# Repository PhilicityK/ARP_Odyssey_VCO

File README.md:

ARP_Odyssey_VCO

Modular Version of the ARP ODYSSEY MKII/III VCO

ABOUT THIS PROJECT

Dreaming of my own modular synthesizer for many years, I've decided to finally start a DIY project. First of all I wanted to build a module which allows me to create sounds. I mean what’s the most exited thing about synthesizers? Right! Turning knobs, altering sounds and waveforms! ;) Therefore I have chosen to build the VCO from an ARP ODYSSEY MKII. If you are not familiar with the ODYSSEY just head over to Youtube and have a quick listen to it. It sounds awesome! :)

ABOUT THE CIRCUIT

The great thing about vintage electronics is the availability of official service and repair manuals. I’ve found one for the ARP ODYSSEY online:
http://www.arpodyssey.com/manuals/Arp%20Odyssey%20Service%20Manual.pdf

With the original schematics at my fingertips it was fairly easy to find the VCO section. I’ve used the latest version of EAGLE (7.7.0) to rebuild the circuit. My goal was to keep it simple by using parts which are still available and easily obtainable. I was able to get everything at my distributor of choice (www.reichelt.de). The VCO operates at +/-15V. It might be possible to use it with +/-12V to create sounds, but at lower voltages the CV-tracking will be most likely inaccurate.
This thread over at electro-music gave me a few ideas on how to design my front panel: 
http://files.electro-music.com/forum/topic-54502.html

BUILDING PROCESS

The PCB is home etched and drilled on my DIY CNC machine. 
Soldering is done with an ERSA soldering iron.
The front panel is created from black acrylic which is CNC machined as well.
I’ve used a white pen with a fine tip to fill in the engraved font.

Have a look at the wiki for further informations on building this module.

IMPORTANT

I have not created the schematics for the ARP Odyssey MKII/III VCO. I have just reworked the layout for all the DIY synth builders out there.

Copyright exists (Rhodes/CBS/ARP). No infringement is intended. The files are for experimental and educational purposes only. All the credits for the schematics go to the copyright holder.

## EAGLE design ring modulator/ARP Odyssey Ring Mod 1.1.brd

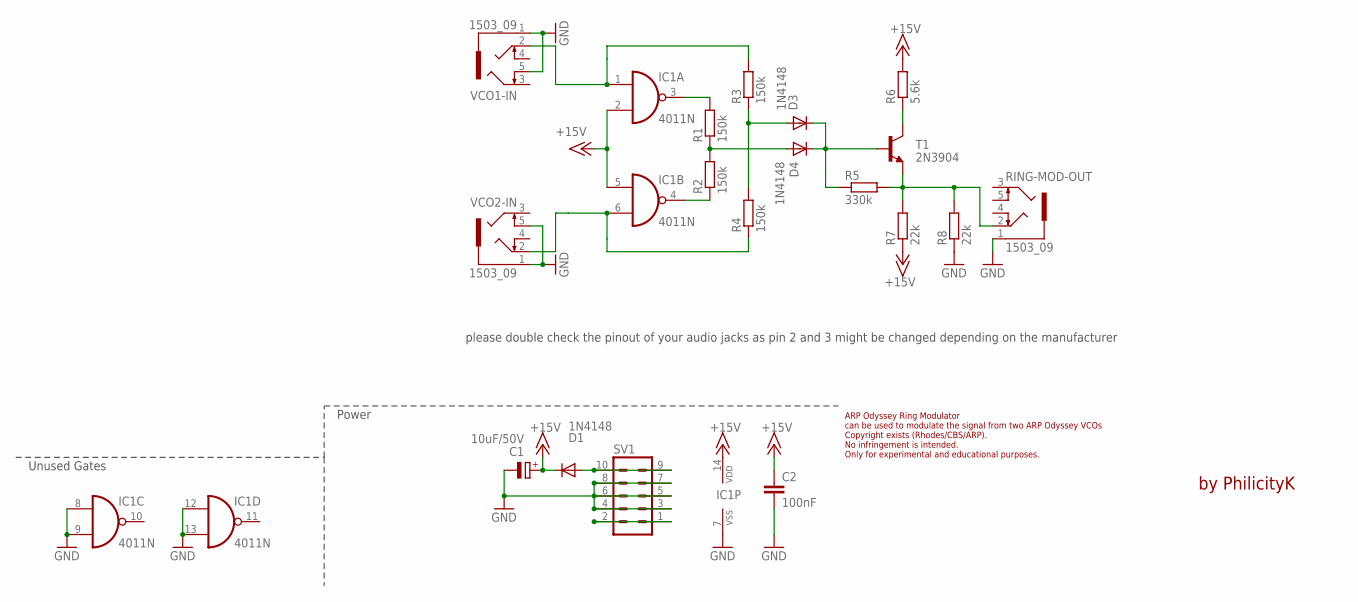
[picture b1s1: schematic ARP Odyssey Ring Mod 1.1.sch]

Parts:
C1: 10uF/50V; E3,5-8
C2: 100nF; C050-024X044
D1, D3, D4: 1N4148; DO35-7
IC1: 4011N; DIL14
R1, R2, R3, R4: 150k; 0207/7
R5: 330k; 0207/7
R6: 5.6k; 0207/7
R7, R8: 22k; 0207/7
RING-MOD-OUT: 1503_09
SV1: ML10
T1: 2N3904; TO92-EBC
VCO1-IN, VCO2-IN: 1503_09

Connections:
+15V: C1.+, C2.1, D1.C, IC1.2 (I1), IC1.5 (I0), IC1.14 (VDD), R6.2, R7.1
GND: C1.-, C2.2, IC1.7 (VSS), IC1.8 (I0), IC1.9 (I1), IC1.12 (I0), IC1.13 (I1), R8.1, RING-MOD-OUT.1, SV1.3, SV1.4, SV1.5, SV1.6, SV1.7, SV1.8, VCO1-IN.1, VCO1-IN.5, VCO2-IN.1, VCO2-IN.5
unnamed: D1.A, SV1.9, SV1.10
unnamed: IC1.3 (O), R1.2
unnamed: IC1.4 (O), R2.1
unnamed: D4.A, R1.1, R2.2
unnamed: SV1.1, SV1.2
unnamed: R5.2, R7.2, R8.2, RING-MOD-OUT.2, T1.E
unnamed: IC1.6 (I1), R4.1, VCO2-IN.2
unnamed: IC1.1 (I0), R3.2, VCO1-IN.2
unnamed: D3.A, R3.1, R4.2
unnamed: D3.C, D4.C, R5.1, T1.B
unnamed: R6.1, T1.C

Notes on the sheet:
ARP Odyssey Ring Modulator can be used to modulate the signal from two ARP Odyssey VCOs Copyright exists (Rhodes/CBS/ARP). No infringement is intended. Only for experimental and educational purposes.
Unused Gates
Power
by PhilicityK
please double check the pinout of your audio jacks as pin 2 and 3 might be changed depending on the manufacturer

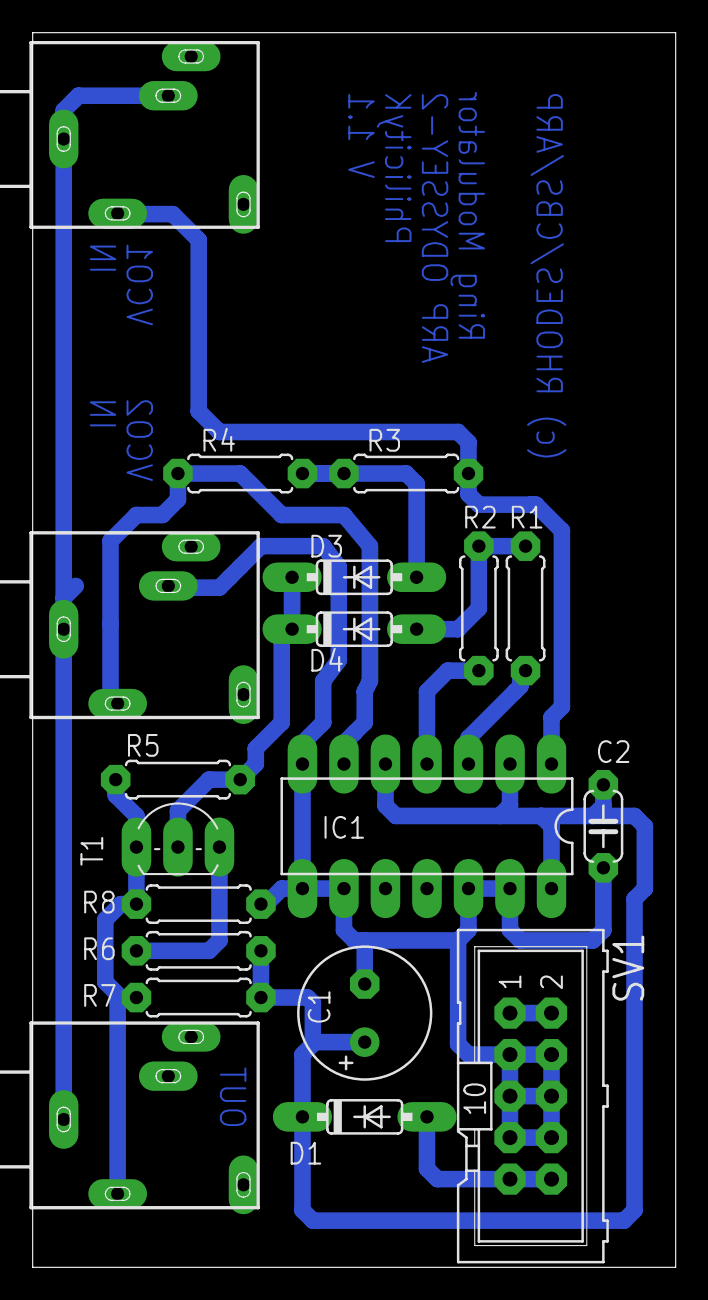
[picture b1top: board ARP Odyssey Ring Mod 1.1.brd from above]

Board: 2 copper layers, 39.4 x 75.6 mm, 19 parts (0 on the bottom side), 13 nets.

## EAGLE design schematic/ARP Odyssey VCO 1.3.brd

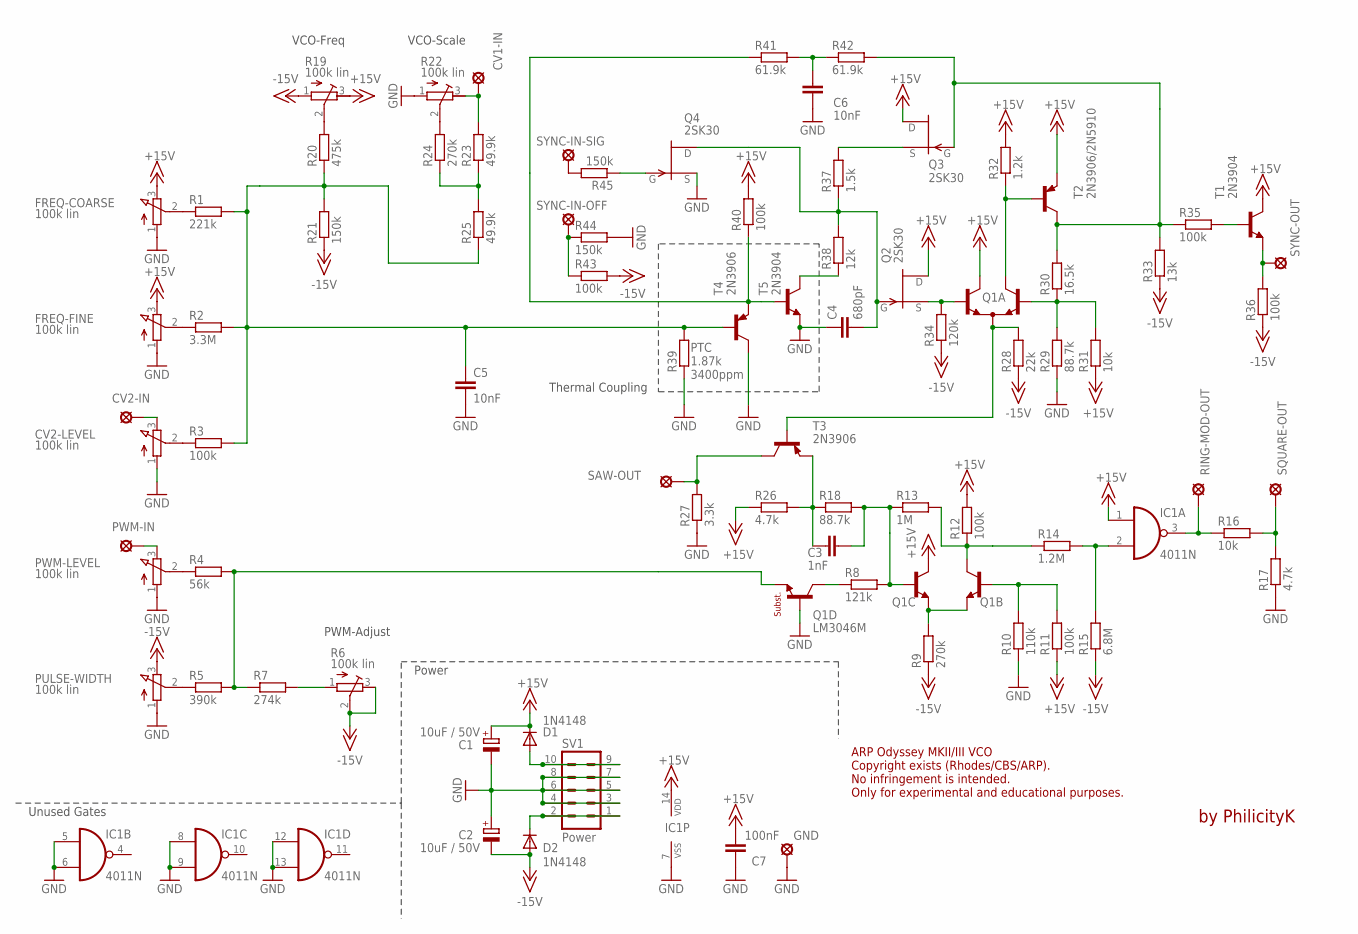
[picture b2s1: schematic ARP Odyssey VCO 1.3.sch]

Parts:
C1, C2: 10uF / 50V; E2,5-6E
C3: 1nF; C050-045X075
C4: 680pF; C050-045X075
C5, C6: 10nF; C050-045X075
C7: 100nF; C050-045X075
CV1-IN, CV2-IN: SE11
CV2-LEVEL: 100k lin; RK11K112
D1, D2: 1N4148; DO35-7
FREQ-COARSE: 100k lin; RK11K112
FREQ-FINE: 100k lin; RK11K112
GND: SE11
IC1: 4011N; DIL14
PULSE-WIDTH: 100k lin; RK11K112
PWM-IN: SE11
PWM-LEVEL: 100k lin; RK11K112
Q1: LM3046M; SO14
Q2, Q3, Q4: 2SK30; TO92
R1: 221k; 0207/7
R2: 3.3M; 0207/7
R3, R11, R12, R35, R36, R40, R43: 100k; 0207/7
R4: 56k; 0207/7
R5: 390k; 0207/7
R6, R19, R22: 100k lin; RTRIM64W
R7: 274k; 0207/7
R8: 121k; 0207/7
R9, R24: 270k; 0207/7
R10: 110k; 0207/7
R13: 1M; 0207/7
R14: 1.2M; 0207/7
R15: 6.8M; 0207/7
R16, R31: 10k; 0207/7
R17, R26: 4.7k; 0207/7
R18, R29: 88.7k; 0207/7
R20: 475k; 0207/7
R21, R44, R45: 150k; 0207/7
R23, R25: 49.9k; 0207/7
R27: 3.3k; 0207/7
R28: 22k; 0207/7
R30: 16.5k; 0207/7
R32: 1.2k; 0207/7
R33: 13k; 0207/7
R34: 120k; 0207/7
R37: 1.5k; 0207/7
R38: 12k; 0207/7
R39: PTC 1.87k; 0207/7
R41, R42: 61.9k; 0207/7
RING-MOD-OUT: SE11
SAW-OUT: SE11
SQUARE-OUT: SE11
SV1: Power; ML10
SYNC-IN-OFF: SE11
SYNC-IN-SIG: SE11
SYNC-OUT: SE11
T1, T5: 2N3904; TO92-EBC
T2: 2N3906/2N5910; TO92-EBC
T3, T4: 2N3906; TO92-EBC

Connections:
+15V: C1.+, C7.2, D1.C, FREQ-COARSE.3 (E), FREQ-FINE.3 (E), IC1.1 (I0), IC1.14 (VDD), Q1.5 (C2), Q1.11 (C), Q2.3 (D), Q3.3 (D), R11.2, R12.2, R19.3 (E), R26.1, R31.2, R32.2, R40.1, T1.C, T2.E
-15V: C2.-, D2.A, PULSE-WIDTH.3 (E), R6.2 (S), R6.3 (E), R9.1, R15.1, R19.1 (A), R21.2, R28.1, R33.1, R34.1, R36.2, R43.2
GND: C1.-, C2.+, C4.1, C5.2, C6.2, C7.1, CV2-LEVEL.1 (A), FREQ-COARSE.1 (A), FREQ-FINE.1 (A), GND.MP, IC1.5 (I0), IC1.6 (I1), IC1.7 (VSS), IC1.8 (I0), IC1.9 (I1), IC1.12 (I0), IC1.13 (I1), PULSE-WIDTH.1 (A), PWM-LEVEL.1 (A), Q1.12 (B), Q4.1 (S), R10.1, R17.1, R22.1 (A), R27.2, R29.1, R39.1, R44.2, SV1.3, SV1.4, SV1.5, SV1.6, SV1.7, SV1.8, T4.C, T5.E
unnamed: D2.C, SV1.1, SV1.2
unnamed: FREQ-COARSE.2 (S), R1.1
unnamed: FREQ-FINE.2 (S), R2.1
unnamed: C5.1, R1.2, R2.2, R3.2, R20.2, R21.1, R25.2, R39.2, T4.B
unnamed: D1.A, SV1.9, SV1.10
unnamed: CV2-LEVEL.2 (S), R3.1
unnamed: CV2-IN.MP, CV2-LEVEL.3 (E)
unnamed: PWM-IN.MP, PWM-LEVEL.3 (E)
unnamed: PWM-LEVEL.2 (S), R4.1
unnamed: PULSE-WIDTH.2 (S), R5.1
unnamed: Q1.13 (E), R4.2, R5.2, R7.1
unnamed: R6.1 (A), R7.2
unnamed: Q1.14 (C), R8.1
unnamed: C3.2, Q1.9 (B), R8.2, R13.1, R18.2
unnamed: Q1.7 (E), Q1.10 (E), R9.2
unnamed: Q1.6 (B), R10.2, R11.1
unnamed: Q1.8 (C), R12.1, R13.2, R14.1
unnamed: IC1.2 (I1), R14.2, R15.2
unnamed: IC1.3 (O), R16.1, RING-MOD-OUT.MP
unnamed: R16.2, R17.2, SQUARE-OUT.MP
unnamed: C3.1, R18.1, R26.2, T3.E
unnamed: R19.2 (S), R20.1
unnamed: R22.2 (S), R24.1
unnamed: R23.2, R24.2, R25.1
unnamed: CV1-IN.MP, R22.3 (E), R23.1
unnamed: Q1.3 (E), R28.2, T3.B
unnamed: R27.1, SAW-OUT.MP, T3.C
unnamed: Q1.2 (B1), R29.2, R30.1, R31.1
unnamed: Q3.2 (G), R30.2, R33.2, R35.2, R42.1, T2.C
unnamed: Q1.1 (C1), R32.1, T2.B
unnamed: Q1.4 (B2), Q2.1 (S), R34.2
unnamed: R36.1, SYNC-OUT.MP, T1.E
unnamed: R35.1, T1.B
unnamed: Q3.1 (S), R37.1
unnamed: C6.1, R41.1, R42.2
unnamed: R38.2, T5.C
unnamed: R40.2, R41.2, T4.E, T5.B
unnamed: R43.1, R44.1, SYNC-IN-OFF.MP
unnamed: Q4.2 (G), R45.1
unnamed: R45.2, SYNC-IN-SIG.MP
unnamed: C4.2, Q2.2 (G), Q4.3 (D), R37.2, R38.1

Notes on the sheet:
PWM-Adjust
VCO-Scale
VCO-Freq
Thermal Coupling
Unused Gates
Power
PTC 1.87k 3400ppm
ARP Odyssey MKII/III VCO Copyright exists (Rhodes/CBS/ARP). No infringement is intended. Only for experimental and educational purposes.
by PhilicityK

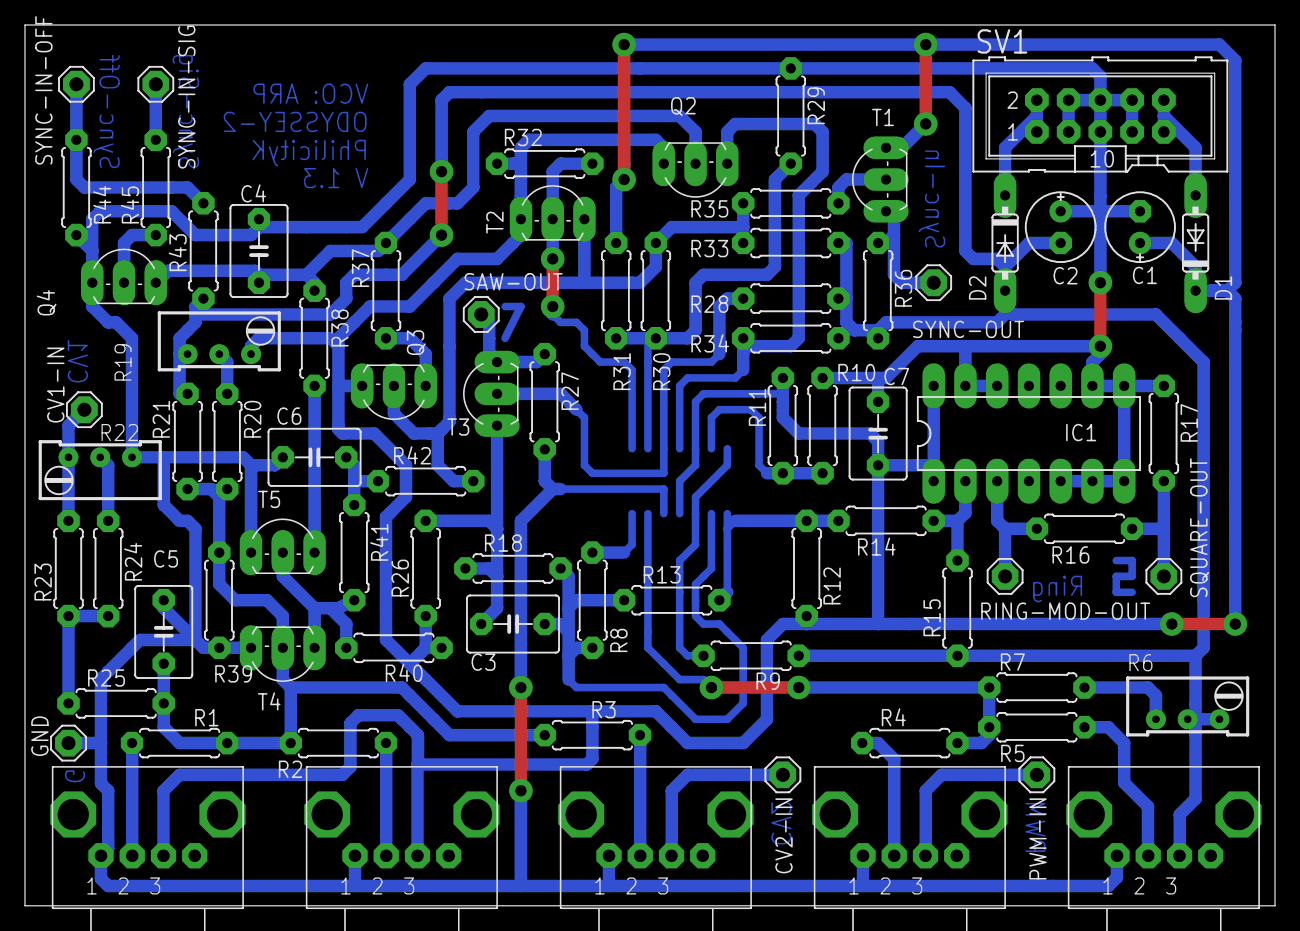
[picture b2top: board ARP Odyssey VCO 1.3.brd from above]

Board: 2 copper layers, 100.0 x 70.5 mm, 80 parts (1 on the bottom side), 44 nets.

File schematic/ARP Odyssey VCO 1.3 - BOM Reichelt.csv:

Qty;Value;Device;Package;Parts;Description;Reichelt; Total (Euro)
2;10uF / 50V;CPOL-EUE2,5-6E;E2,5-6E;C1, C2;POLARIZED CAPACITOR, European symbol;RAD FC 10/50;0,20
1;1nF;C-EU050-045X075;C050-045X075;C3;CAPACITOR, European symbol;FKP2-63 1,0N;0,13
1;680pF;C-EU050-045X075;C050-045X075;C4;CAPACITOR, European symbol;FKP2-100 680P;0,13
2;10nF;C-EU050-045X075;C050-045X075;C5, C6;CAPACITOR, European symbol;FKP2-63 10N;0,15
1;100nF;C-EU050-045X075;C050-045X075;C7;CAPACITOR, European symbol;MKS2-63 100N;0,13
5;100k lin;RK11K112;RK11K112;CV2-LEVEL, FREQ-COARSE, FREQ-FINE, PULSE-WIDTH, PWM-LEVEL;ALPS-Potentiometer;RK11K112-LIN100K;6,75
2;1N4148;1N4148DO35-7;DO35-7;D1, D2;DIODE;1N 4148;0,08
1;4011N;4011N;DIL14;IC1;Quad 2-input NAND;MOS 4011;0,24
1;LM3046M/NOPB;LM3046M/NOPB;SO14;Q1;Texas Instruments LM3046;LM 3046 M;0,80
3;2SK30;2SK30;TO92;Q2, Q3, Q4;Transistor N-FET;2SK 30;2,58
1;221k;R-EU_0207/7;0207/7;R1;RESISTOR, European symbol;METALL 221K;0,08
1;110k;R-EU_0207/7;0207/7;R10;RESISTOR, European symbol;METALL 110K;0,08
1;1M;R-EU_0207/7;0207/7;R13;RESISTOR, European symbol;METALL 1,00M;0,08
1;1.2M;R-EU_0207/7;0207/7;R14;RESISTOR, European symbol;METALL 1,20M;0,08
1;6.8M;R-EU_0207/7;0207/7;R15;RESISTOR, European symbol;METALL 6,80M;0,08
2;10k;R-EU_0207/7;0207/7;R16, R31;RESISTOR, European symbol;METALL 10,0K;0,16
2;4.7k;R-EU_0207/7;0207/7;R17, R26;RESISTOR, European symbol;METALL 4,70K;0,16
2;88.7k;R-EU_0207/7;0207/7;R18, R29;RESISTOR, European symbol;METALL 88,7K;0,16
1;3.3M;R-EU_0207/7;0207/7;R2;RESISTOR, European symbol;METALL 3,30M;0,08
1;475k;R-EU_0207/7;0207/7;R20;RESISTOR, European symbol;METALL 475K;0,08
3;150k;R-EU_0207/7;0207/7;R21, R44, R45;RESISTOR, European symbol;METALL 150K;0,25
2;49.9k;R-EU_0207/7;0207/7;R23, R25;RESISTOR, European symbol;METALL 49,9K;0,16
1;3.3k;R-EU_0207/7;0207/7;R27;RESISTOR, European symbol;METALL 3,30K;0,08
1;22k;R-EU_0207/7;0207/7;R28;RESISTOR, European symbol;METALL 22,0K;0,08
7 (10);100k;R-EU_0207/7;0207/7;R3, R11, R12, R35, R36, R40, R43;RESISTOR, European symbol (10pcs are cheaper than 7);METALL 100K;0,49
1;16.5k;R-EU_0207/7;0207/7;R30;RESISTOR, European symbol;METALL 16,5K;0,08
1;1.2k;R-EU_0207/7;0207/7;R32;RESISTOR, European symbol;METALL 1,20K;0,08
1;13k;R-EU_0207/7;0207/7;R33;RESISTOR, European symbol;METALL 13,0K;0,08
1;120k;R-EU_0207/7;0207/7;R34;RESISTOR, European symbol;METALL 120K;0,08
1;1.5k;R-EU_0207/7;0207/7;R37;RESISTOR, European symbol;METALL 1,50K;0,08
1;12k;R-EU_0207/7;0207/7;R38;RESISTOR, European symbol;METALL 12,0K;0,08
1;PTC 1.87k;R-EU_0207/7;0207/7;R39;PTC  (TEMPCO 1.87k 3400ppm would be better but isn't avaliable from Reichelt);KTY 81-210;0,63
1;56k;R-EU_0207/7;0207/7;R4;RESISTOR, European symbol;METALL 56,0K;0,08
2;61.9k;R-EU_0207/7;0207/7;R41, R42;RESISTOR, European symbol;METALL 62,0K;0,16
1;390k;R-EU_0207/7;0207/7;R5;RESISTOR, European symbol;METALL 390K;0,08
3;100k lin;R-TRIMM64W;RTRIM64W;R6, R19, R22;Trimm resistor;64W-100K;0,96
1;274k;R-EU_0207/7;0207/7;R7;RESISTOR, European symbol;METALL 274K;0,08
1;121k;R-EU_0207/7;0207/7;R8;RESISTOR, European symbol;METALL 121K;0,08
2;270k;R-EU_0207/7;0207/7;R9, R24;RESISTOR, European symbol;METALL 270K;0,08
1;Power;ML10;ML10;SV1;HARTING;WSL 10G;0,09
2;2N3904;2N3904-NPN-TO92-EBC;TO92-EBC;T1, T5;NPN Transistror;2N 3904;0,16
1;2N3906/2N5910;2N3906-PNP-TO92-EBC;TO92-EBC;T2;PNP Transistror;2N 3906;0,04
2;2N3906;2N3906-PNP-TO92-EBC;TO92-EBC;T3, T4;PNP Transistror;2N 3906;0,08
1;;;;;Single sided PCB;BEL 75X100-1;0,99
8;;;;;3,5mm switched mono jacks;LUM 1502-03;6,88
;;;;;;;
;;;;;;;24,22
;;;;;;;

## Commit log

2016-12-20 ARP Odyssey VCO 1.3 - Schematic
2016-12-20 EAGLE files, PCB and BOM
2016-12-20 BOM Screenshot
2016-12-20 added images of the board
2016-12-21 documentation
2016-12-21 information
2016-12-23 minor fixes
2016-12-31 added images and panel design
2016-12-31 pictures
2017-01-02 added the ring modulator
